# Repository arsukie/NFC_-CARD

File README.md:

# NFC Hacker Card 
This is  Design of my NFC Bussiness Card or You can call it a Hacker Card as well. I was starting out the Hardware and found this thing as a cool project and Let me know the basics so I build this Thing.

### Project function
This is a NFC card mean it can read and write the NFC commands and exectue them as well. It uses NT3H2111W0FHKH IC for the NFC handeling and a 25x48 antenna , a LED light , a 47Ω Resistor and 220nF Capacitor. The led Will blink whenever the antenna harvests the energy.

# NFC Business Card - Bill of Materials
 
An NFC-powered business card. The NT3H2111W0FHKH handles NFC communication and harvests energy from the phone to light up an LED — no battery needed. The antenna is engraved directly on the PCB.
 
## Components
 
- **NT3H2111W0FHKH** - NFC chip, the main component of the card. Handles NFC functionality and harvests energy from the phone to light up the LED.
- **~2V LED** - using C2296 (also known as 17-21SUYC/TR8), but any similar 2V LED works.
- **47Ω resistor**
- **220nF capacitor**
- **NFC antenna** - engraved on the PCB itself, no separate part needed.
- 
## Bill of Materials
 
| No. | Quantity | Comment | Designator | Footprint | Value | Manufacturer Part | Manufacturer | Supplier Part | Supplier |
|---|---|---|---|---|---|---|---|---|---|
| 1 | 1 | 220nF | C1 | C0603 | | CL10B224KA8NNNC | SAMSUNG | C21120 | [LCSC](https://www.lcsc.com/product-detail/C21120.html?s_z=n_q_CL10B224KA8NNNC&spm=wm.fly.bg.0.xh&lcsc_vid=EgdXVwICRgMMUQdTT1AKU1ZfQgRfUVFSEVRcXldUEQIxVlNeQlNdVFJSRFRbVTsOAxUeFF5JWBYZEEoKFBINSQcJGk4MCAlJGBEaDgsIBA%3D%3D) |
| 2 | 1 | 17-21SUYC/TR8 | LED1 | LED0805-R-RD | | KT-0805 Yellow LED | KENTO | C2296 | [LCSC](https://www.lcsc.com/product-detail/C2296.html?s_z=n_q_KT-0805%2520Yellow%2520LED&spm=wm.fly.bg.0.xh&lcsc_vid=EgdXVwICRgMMUQdTT1AKU1ZfQgRfUVFSEVRcXldUEQIxVlNeQlNdVFNVRVdeUTsOAxUeFF5JWBYZEEoKFBINSQcJGk4eFQsCAgIaSgADAwAHC0slRVBfVVRIHxUDCw%3D%3D) |
| 3 | 1 | 47Ω | R1 | R0603 | | 0603WAF470JT5E | UNI-ROYAL | C23182 | [LCSC](https://www.lcsc.com/product-detail/C23182.html?s_z=s_p_0603WAF470JT5E&spm=wm.fly.bg.0.xh&lcsc_vid=EgdXVwICRgMMUQdTT1AKU1ZfQgRfUVFSEVRcXldUEQIxVlNeQlNdVFNfTlVXUTsOAxUeFF5JWBYZEEoKFBINSQcJGk4dAgUUFAk%3D) |
| 4 | 1 | NT3H2111W0FHKH | U1 | XQFN-8_L1.6-W1.6-P0.50-BL_NT3H2111W0FHKH | | NT3H2111W0FHKH | NXP | C710403 | [LCSC](https://www.lcsc.com/product-detail/C710403.html?s_z=n_q_NT3H2111W0FHKH&spm=wm.fly.bg.0.xh&lcsc_vid=EgdXVwICRgMMUQdTT1AKU1ZfQgRfUVFSEVRcXldUEQIxVlNeQlNdVFxVRVFbVDsOAxUeFF5JWBYZEEoKFBINSQcJGk4eFQsCAgIaSgADAwAHC0slRVJfX1ZIHxUDCw%3D%3D) |
 
## PCB & Shipping
 
| Type | Item | Description | Qty | Build Time | Price |
|---|---|---|---|---|---|
| PCB | Gerber_Bussiness_card_Y9 | PCB prototype: Y9-13163216A, Black, 1.6 Thickness, HASL(with lead) | 5 pcs | 24 hours | $4.00 |
| PCBA | Gerber_Bussiness_card_Y9 | Economic PCBA: SMT026082762821-13163216A, Assemble top side | 2 pcs | 1 - 2 days | $15.78 |
 
| | |
|---|---|
| **PCB (Merchandise)** | $19.78 |
| Shipping | $16.01 |
| **Subtotal** | **$35.79** |
## Cart

### NOTE 

THE NFC ANTENNA USED IN THE SCHEMATIC IS FROM THE USER CONTRIBUTED LIBRARY FROM THE EASYEDA SO YOU MIGHT NEED TO GET THE PCB OR YOU CAN USE ANY ANTENNA THAT WORKS FOR NFC AND SUPPORTS NT3H2111W0FHKH IC. I AM USING A 25X48 FOOTPRINT AND IT IS ENGRAVED ON THE COPPER LAYER OF THE PCB.

# Schematics

# Boardview

# 3D View 

### Author - Arsukie

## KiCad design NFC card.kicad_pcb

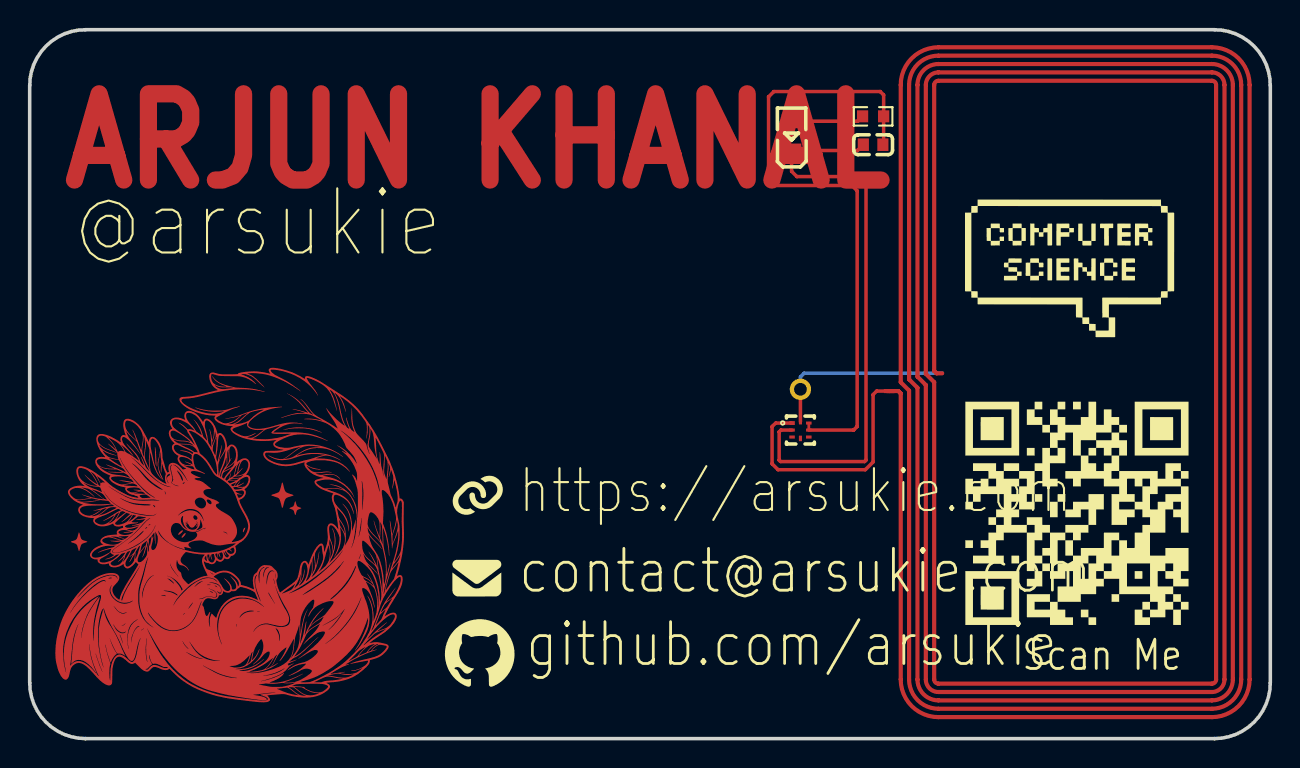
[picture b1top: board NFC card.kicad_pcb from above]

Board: 2 copper layers, 88.9 x 50.8 mm, 5 parts (0 on the bottom side), 5 nets.

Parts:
1: 25X48MM_NFC_ANTENNA
C1: C0603
LED1: LED0805-R-RD
R1: R0603
U1: XQFN-8_L1.6-W1.6-P0.50-BL_NT3H2111W0FHKH

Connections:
R1_1: LED1.1, R1.1
U1_1: 1.P$1, U1.1
U1_2: C1.1, LED1.2, U1.2
U1_6: C1.2, R1.2, U1.6, U1.7
U1_8: 1.P$2, U1.8
